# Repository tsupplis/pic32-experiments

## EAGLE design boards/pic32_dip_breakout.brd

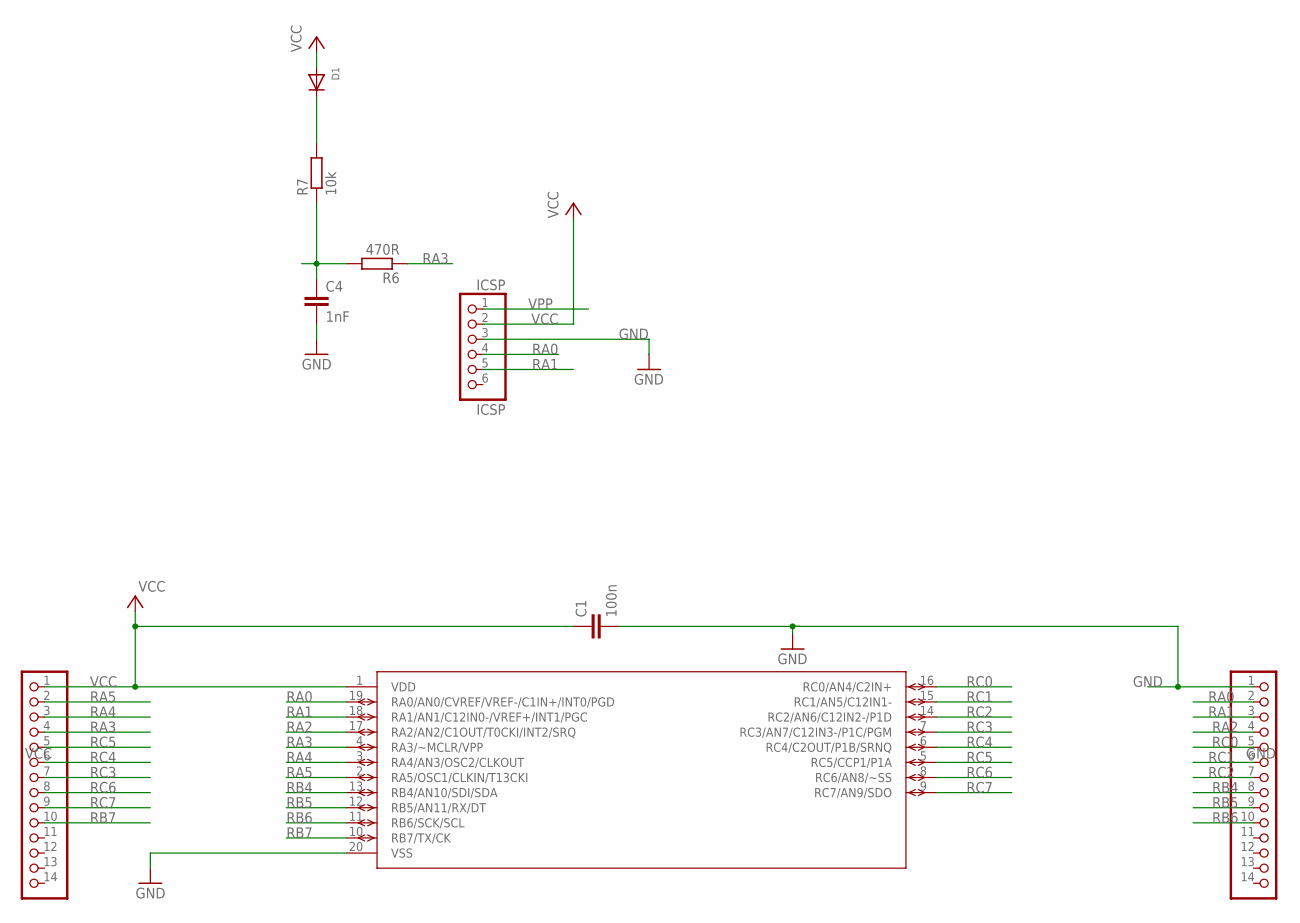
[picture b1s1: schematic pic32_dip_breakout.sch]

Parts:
C1: 100n; C0805
C4: 1nF; C0805
D1: DIODESOD-323F; SOD-323F
GND: PINHD-1X14; 1X14
ICSP: ICSP; 1X06
R6: 470R; R0805
R7: 10k; R0805
U$1: PIC18F14K22-I/P; DIP254P762X533-20
VCC: PINHD-1X14; 1X14

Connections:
GND: C1.2, C4.2, GND.1, ICSP.3, U$1.20 (VSS)
unnamed: D1.C, R7.2
RA0: GND.2, ICSP.4, U$1.19 (RA0/AN0/CVREF/VREF-/C1IN+/INT0/PGD)
RA1: GND.3, ICSP.5, U$1.18 (RA1/AN1/C12IN0-/VREF+/INT1/PGC)
RA2: GND.4, U$1.17 (RA2/AN2/C1OUT/T0CKI/INT2/SRQ)
RA3: R6.1, U$1.4 (RA3/~MCLR/VPP), VCC.4
RA4: U$1.3 (RA4/AN3/OSC2/CLKOUT), VCC.3
RA5: U$1.2 (RA5/OSC1/CLKIN/T13CKI), VCC.2
RB4: GND.8, U$1.13 (RB4/AN10/SDI/SDA)
RB5: GND.9, U$1.12 (RB5/AN11/RX/DT)
RB6: GND.10, U$1.11 (RB6/SCK/SCL)
RB7: U$1.10 (RB7/TX/CK), VCC.10
RC0: GND.5, U$1.16 (RC0/AN4/C2IN+)
RC1: GND.6, U$1.15 (RC1/AN5/C12IN1-)
RC2: GND.7, U$1.14 (RC2/AN6/C12IN2-/P1D)
RC3: U$1.7 (RC3/AN7/C12IN3-/P1C/PGM), VCC.7
RC4: U$1.6 (RC4/C2OUT/P1B/SRNQ), VCC.6
RC5: U$1.5 (RC5/CCP1/P1A), VCC.5
RC6: U$1.8 (RC6/AN8/~SS), VCC.8
RC7: U$1.9 (RC7/AN9/SDO), VCC.9
VCC: C1.1, D1.A, ICSP.2, U$1.1 (VDD), VCC.1
VPP: C4.1, ICSP.1, R6.2, R7.1

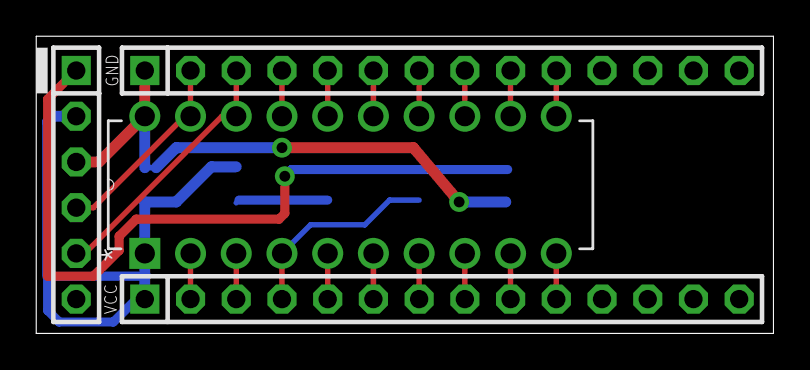
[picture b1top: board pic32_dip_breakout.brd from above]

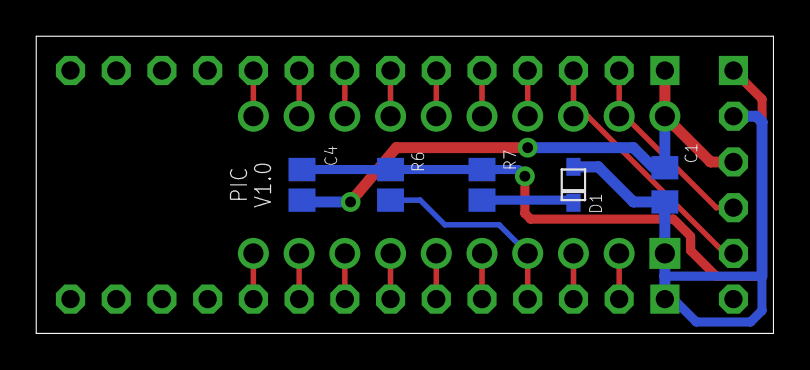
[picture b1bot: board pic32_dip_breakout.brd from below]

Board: 2 copper layers, 41.0 x 16.5 mm, 9 parts (5 on the bottom side), 22 nets.

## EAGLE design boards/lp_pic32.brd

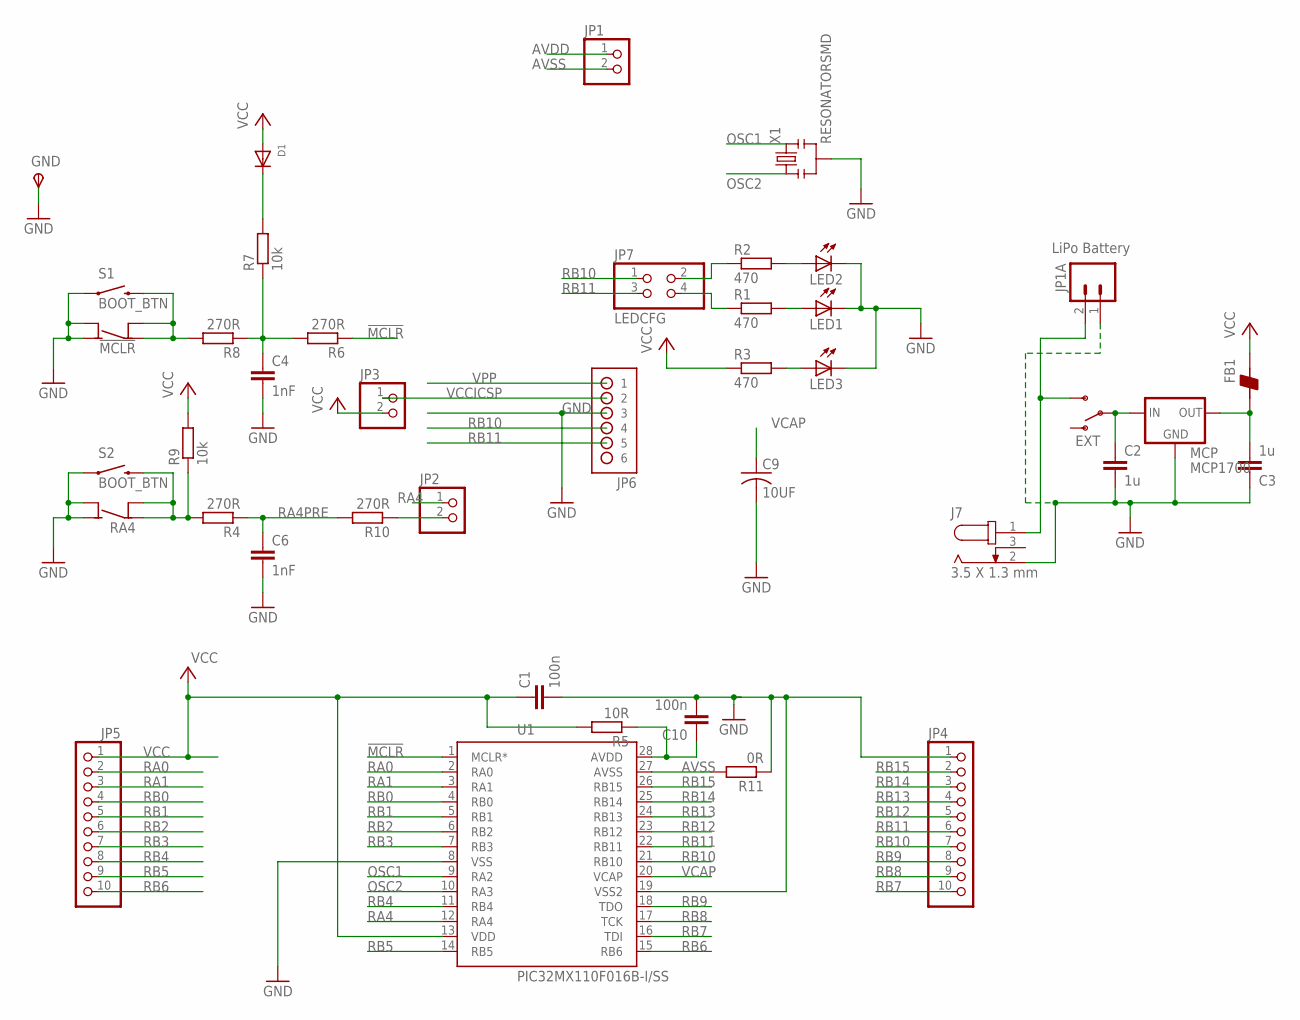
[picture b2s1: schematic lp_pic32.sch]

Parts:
!MCLR: !MCLR; 6MMTACTILE_4PIN
C1, C10: 100n; C0805
C2, C3: 1u; C0805
C4, C6: 1nF; C0805
C9: 10UF; C1206
D1: DIODESOD-323F; SOD-323F
FB1: BEAD-0805; 0805
GND: TPSTP20R; TP20R
J7: 3.5 X 1.3 mm; 3.5X1.3MM_DC_JACK
JP1, JP2, JP3: PINHD-1X2; 1X02
JP1A: LiPo Battery; JST-2-PTH
JP4, JP5: PH1X10OCT076; PH1X10OCT76
JP6: No Load; HDR-1X6_OFFSET
JP7: LEDCFG; 2X02
LED1, LED2, LED3: 0; CHIPLED_1206
MCP: MCP1700; SOT-23
ON: EXT; SWITCH-SPDT
R1, R2, R3: 470; R0805
R4, R6, R8, R10: 270R; R0805
R5: 10R; R0805
R7, R9: 10k; R0805
R11: 0R; R0805
RA4: RA4; 6MMTACTILE_4PIN
S1, S2: BOOT_BTN; TACTILE-SWITCH-1101NE
U1: PIC32MX110F016B-I/SS; SOP65P780X200-28N
X1: RESONATORSMD; RESONATOR-SMD

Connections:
!MCLR: R6.1, U1.1 (MCLR*)
AVDD: C10.1, JP1.1, R5.1, U1.28 (AVDD)
AVSS: JP1.2, R11.2, U1.27 (AVSS)
GND: !MCLR.A1 (NO), !MCLR.A2 (NO), C1.2, C2.2, C3.1, C4.2, C6.2, C9.2, C10.2, GND.TP, J7.2, JP1A.1, JP4.1, JP6.3, LED1.C, LED2.C, LED3.C, MCP.1 (GND), R11.1, RA4.A1 (NO), RA4.A2 (NO), S1.1, S2.1, U1.8 (VSS), U1.19 (VSS2), X1.2
unnamed: JP7.2, R2.1
unnamed: JP7.4, R1.1
unnamed: C2.1, MCP.3 (IN), ON.2
unnamed: R4.2, R9.1, RA4.B1 (COM), RA4.B2 (COM), S2.2
unnamed: !MCLR.B1 (COM), !MCLR.B2 (COM), R8.2, S1.2
unnamed: C3.2, FB1.1, MCP.2 (OUT)
unnamed: D1.C, R7.2
unnamed: JP2.2, R10.1
unnamed: LED3.A, R3.2
unnamed: LED1.A, R1.2
unnamed: LED2.A, R2.2
OSC1: U1.9 (RA2), X1.3
OSC2: U1.10 (RA3), X1.1
RA0: JP5.2, U1.2 (RA0)
RA1: JP5.3, U1.3 (RA1)
RA4: JP2.1, U1.12 (RA4)
RA4PRE: C6.1, R4.1, R10.2
RB0: JP5.4, U1.4 (RB0)
RB1: JP5.5, U1.5 (RB1)
RB2: JP5.6, U1.6 (RB2)
RB3: JP5.7, U1.7 (RB3)
RB4: JP5.8, U1.11 (RB4)
RB5: JP5.9, U1.14 (RB5)
RB6: JP5.10, U1.15 (RB6)
RB7: JP4.10, U1.16 (TDI)
RB8: JP4.9, U1.17 (TCK)
RB9: JP4.8, U1.18 (TDO)
RB10: JP4.7, JP6.4, JP7.1, U1.21 (RB10)
RB11: JP4.6, JP6.5, JP7.3, U1.22 (RB11)
RB12: JP4.5, U1.23 (RB12)
RB13: JP4.4, U1.24 (RB13)
RB14: JP4.3, U1.25 (RB14)
RB15: JP4.2, U1.26 (RB15)
VCAP: C9.1, U1.20 (VCAP)
VCC: C1.1, D1.A, FB1.2, JP3.2, JP5.1, R3.1, R5.2, R9.2, U1.13 (VDD)
VCCEXT: J7.1, JP1A.2, ON.3 (S)
VCCICSP: JP3.1, JP6.2
VPP: C4.1, JP6.1, R6.2, R7.1, R8.1

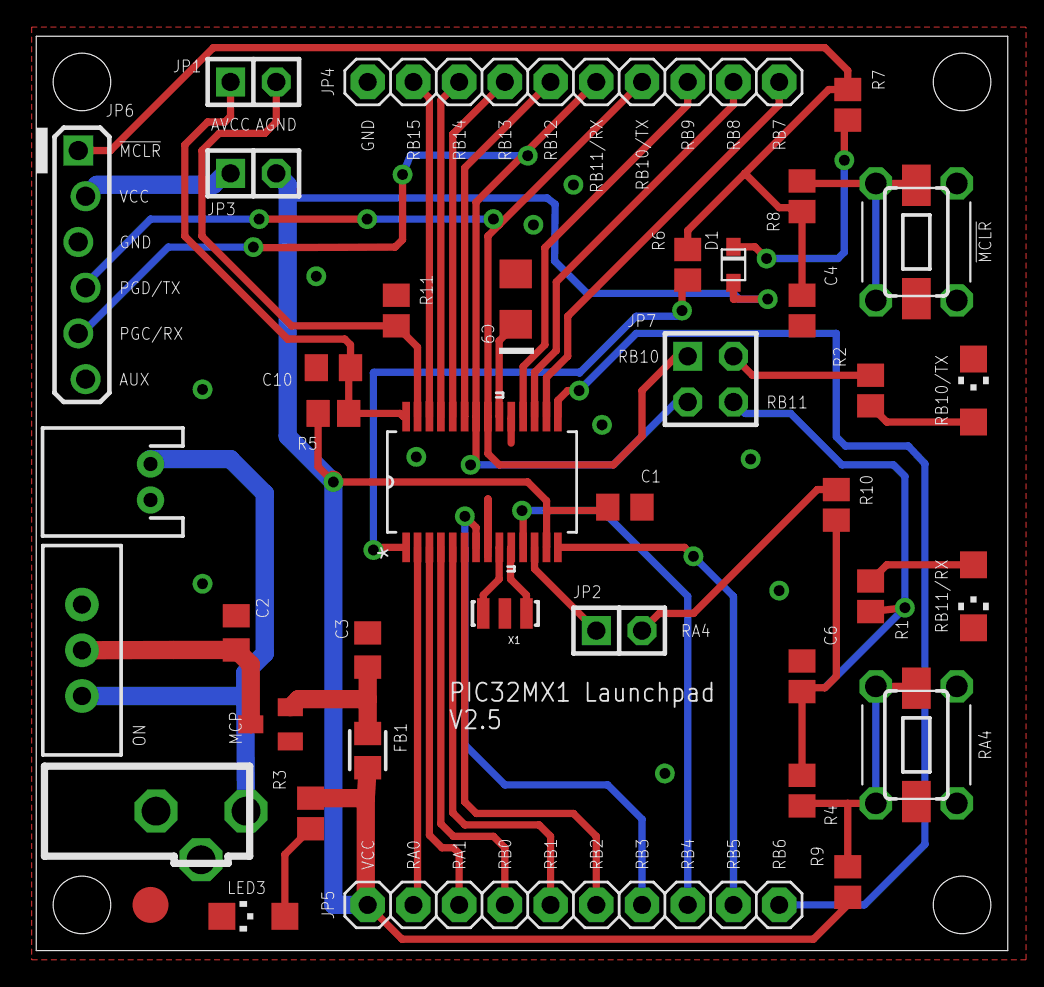
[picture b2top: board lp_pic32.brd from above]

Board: 2 copper layers, 54.0 x 50.8 mm, 41 parts (0 on the bottom side), 42 nets.

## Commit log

2016-04-05 fix naming

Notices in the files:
parts and their libraries:
SparkFun: Licensing: CC v3.0 Share-Alike You are welcome to use this library for commercial purposes.
SparkFun-Electromechanical: Licensing: Creative Commons ShareAlike 4.0 International - https://creativecommons.org/licenses/by-sa/4.0
